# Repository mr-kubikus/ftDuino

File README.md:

# ftDuino
ftDuino controller board

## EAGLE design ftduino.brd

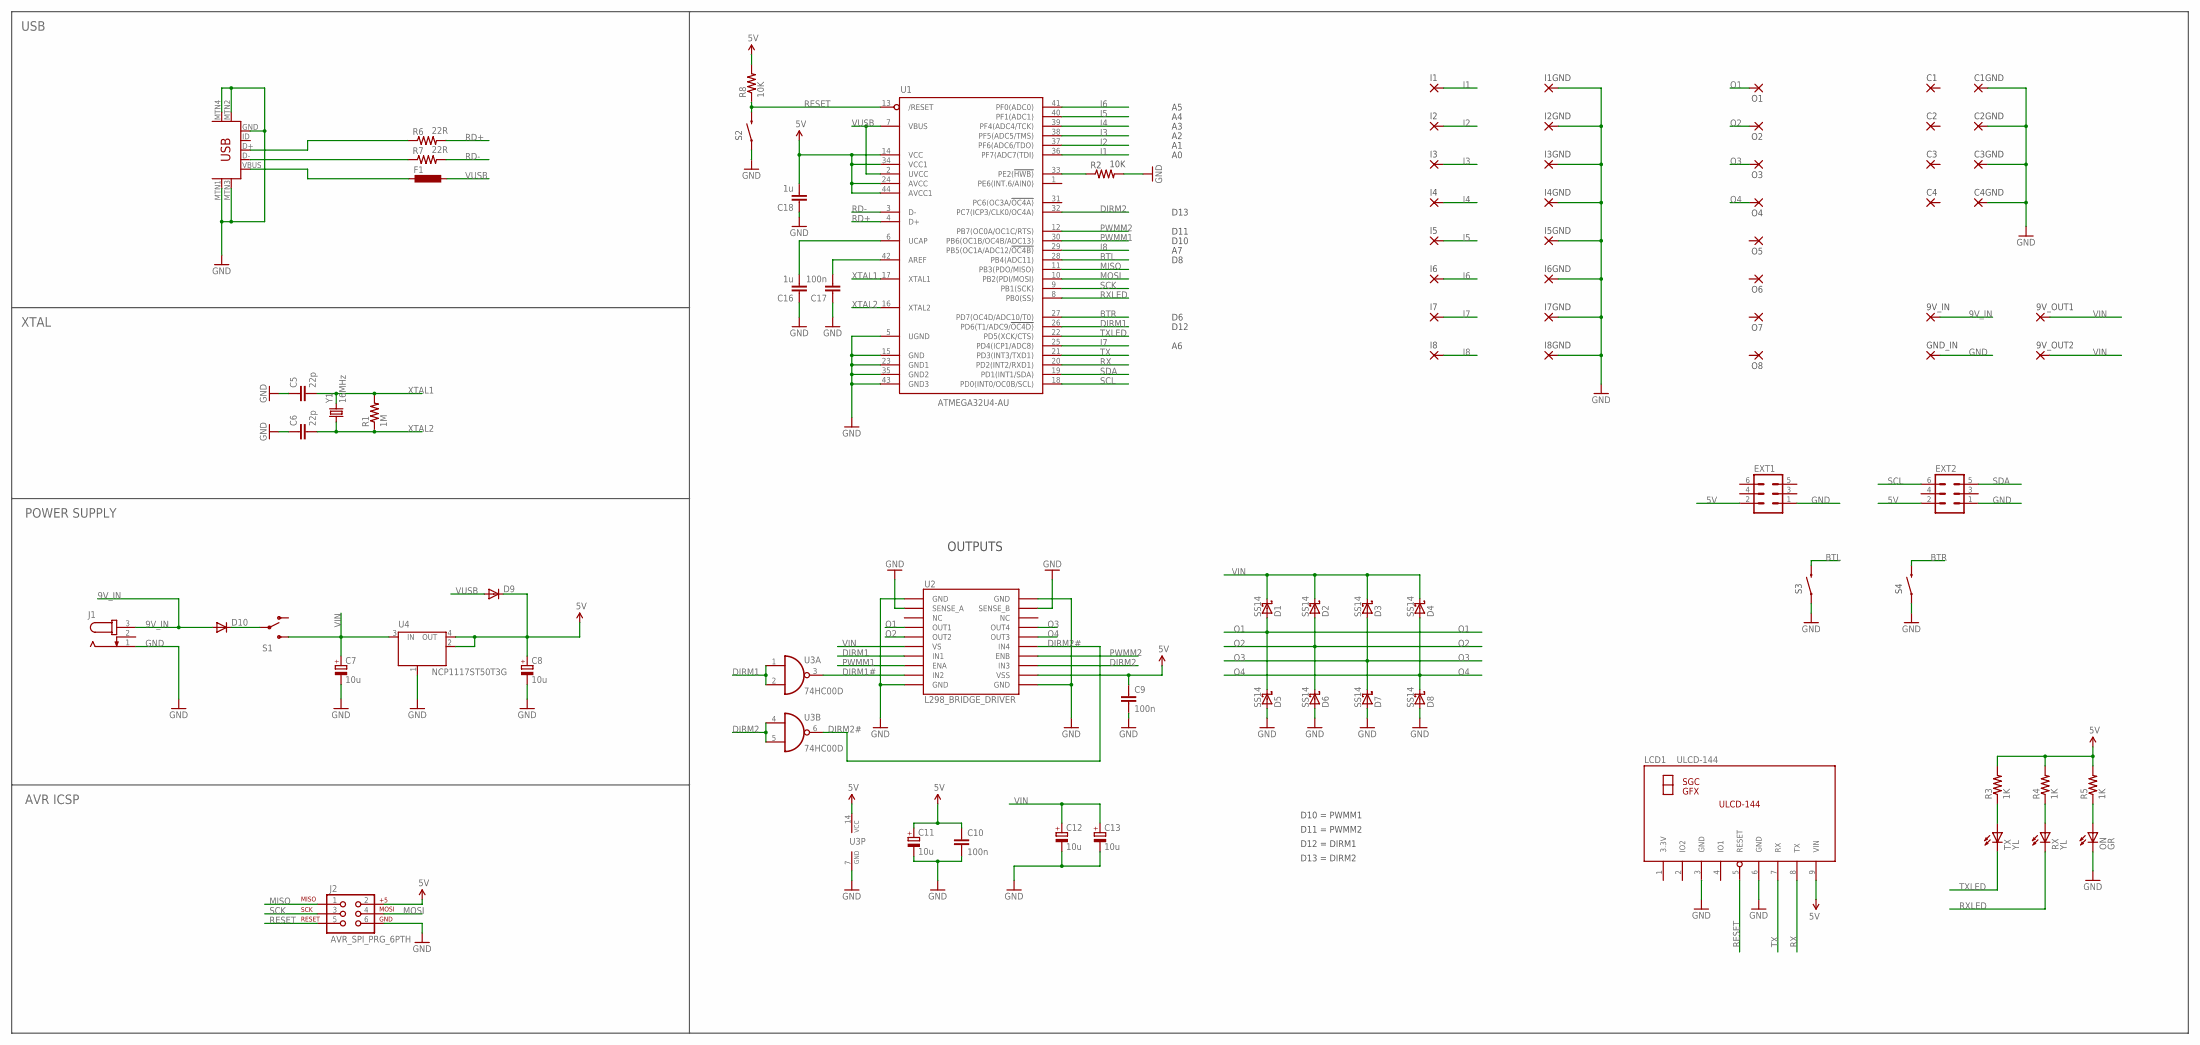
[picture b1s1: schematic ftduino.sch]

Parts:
9V_IN, 9V_OUT1, 9V_OUT2: 5,0/3,2
C1, C1GND, C2, C2GND, C3, C3GND, C4, C4GND: 5,0/3,2
C5, C6: 22p; 0603-CAP
C7, C8, C11, C12, C13: 10u; SMC_B
C9, C10, C17: 100n; 0603-CAP
C16, C18: 1u; 0603-CAP
D1, D2, D3, D4, D5, D6, D7, D8: SS14; SMA
D9, D10: DIODE-SMB; SMB
EXT1, EXT2: MA03-2
F1: L-EUL1812; L1812
GND_IN: 5,0/3,2
I1, I1GND, I2, I2GND, I3, I3GND, I4, I4GND, I5, I5GND, I6, I6GND, I7, I7GND, I8, I8GND: 5,0/3,2
J1: JACK-PLUG1; JK3.5/1.8
J2: AVR_SPI_PRG_6PTH; 2X3
LCD1: ULCD-144
O1, O2, O3, O4, O5, O6, O7, O8: 5,0/3,2
ON: GR; CHIPLED_0805
R1: 1M; 0603-RES
R2, R8: 10K; 0603-RES
R3, R4, R5: 1K; 0603-RES
R6, R7: 22R; 0603-RES
RX: YL; CHIPLED_0805
S1: SWITCH-SPSTPTH; SWITCH-SPDT
S2, S3, S4: SWITCH-MOMENTARY-2PTH; TACTILE-PTH
TX: YL; CHIPLED_0805
U1: ATMEGA32U4-AU; TQFP44
U2: L298_BRIDGE_DRIVER; POWERSO20
U3: 74HC00D; SO14
U4: NCP1117ST50T3G; SOT223
X1: USB-MINIB-5PIN; USB-MINIB
Y1: 16MHz; CTS406

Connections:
3.3V: LCD1.1 (3.3V)
5V: C8.+, C9.1, C10.1, C11.+, C18.2, D9.C, EXT1.2, EXT2.2, J2.2, LCD1.9 (VIN), R3.2, R4.2, R5.2, R8.2, U1.14 (VCC), U1.24 (AVCC), U1.34 (VCC1), U1.44 (AVCC1), U2.12 (VSS), U3.14 (VCC), U4.2 (OUT), U4.4 (OUT)
9V_IN: 9V_IN.1, D10.A, J1.3
BTL: S3.3 (2), U1.28 (PB4(ADC11))
BTR: S4.3 (2), U1.27 (PD7(OC4D/ADC10/T0))
DIRM1: U1.26 (PD6(T1/ADC9/!OC4D)), U2.7 (IN1), U3.1 (I0), U3.2 (I1)
DIRM1#: U2.9 (IN2), U3.3 (O)
DIRM2: U1.32 (PC7(ICP3/CLK0/OC4A)), U2.13 (IN3), U3.4 (I0), U3.5 (I1)
DIRM2#: U2.15 (IN4), U3.6 (O)
GND: C1GND.1, C2GND.1, C3GND.1, C4GND.1, C5.1, C6.1, C7.-, C8.-, C9.2, C10.2, C11.-, C12.-, C13.-, C16.1, C17.1, C18.1, D5.A, D6.A, D7.A, D8.A, EXT1.1, EXT2.1, GND_IN.1, I1GND.1, I2GND.1, I3GND.1, I4GND.1, I5GND.1, I6GND.1, I7GND.1, I8GND.1, J1.1, J2.6, LCD1.3 (GND), LCD1.6 (GND), ON.C, R2.2, S2.1, S3.1, S4.1, U1.5 (UGND), U1.15 (GND), U1.23 (GND1), U1.35 (GND2), U1.43 (GND3), U2.1 (GND), U2.2 (SENSE_A), U2.10 (GND), U2.11 (GND), U2.19 (SENSE_B), U2.20 (GND), U3.7 (GND), U4.1 (GND/ADJ), X1.GND, X1.MTN1 (MTN2), X1.MTN2 (MTN3), X1.MTN3 (MTN1), X1.MTN4
I1: I1.1, U1.36 (PF7(ADC7(TDI))
I2: I2.1, U1.37 (PF6(ADC6/TDO))
I3: I3.1, U1.38 (PF5(ADC5/TMS))
I4: I4.1, U1.39 (PF4(ADC4/TCK))
I5: I5.1, U1.40 (PF1(ADC1))
I6: I6.1, U1.41 (PF0(ADC0))
I7: I7.1, U1.25 (PD4(ICP1/ADC8))
I8: I8.1, U1.29 (PB5(OC1A/ADC12/!OC4B))
MISO: J2.1, U1.11 (PB3(PDO/MISO))
MOSI: J2.4, U1.10 (PB2(PDI/MOSI))
unnamed: C17.2, U1.42 (AREF)
unnamed: C16.2, U1.6 (UCAP)
unnamed: R3.1, TX.A
unnamed: R4.1, RX.A
unnamed: ON.A, R5.1
unnamed: R6.1, X1.D+
unnamed: R7.1, X1.D-
unnamed: R2.1, U1.33 (PE2(!HWB))
unnamed: F1.2, X1.VBUS
unnamed: D10.C, S1.2
O1: D1.A, D5.C, O1.1, U2.4 (OUT1)
O2: D2.A, D6.C, O2.1, U2.5 (OUT2)
O3: D3.A, D7.C, O3.1, U2.17 (OUT4)
O4: D4.A, D8.C, O4.1, U2.16 (OUT3)
PWMM1: U1.30 (PB6(OC1B/OC4B/ADC13)), U2.8 (ENA)
PWMM2: U1.12 (PB7(OC0A/OC1C/RTS)), U2.14 (ENB)
RD+: R6.2, U1.4 (D+)
RD-: R7.2, U1.3 (D-)
RESET: J2.5, LCD1.5 (RESET), R8.1, S2.3 (2), U1.13 (/RESET)
RX: LCD1.8 (TX), U1.20 (PD2(INT2/RXD1))
RXLED: RX.C, U1.8 (PB0(SS))
SCK: J2.3, U1.9 (PB1(SCK))
SCL: EXT2.6, U1.18 (PD0(INT0/OC0B/SCL))
SDA: EXT2.5, U1.19 (PD1(INT1/SDA))
TX: LCD1.7 (RX), U1.21 (PD3(INT3/TXD1))
TXLED: TX.C, U1.22 (PD5(XCK/CTS))
VIN: 9V_OUT1.1, 9V_OUT2.1, C7.+, C12.+, C13.+, D1.C, D2.C, D3.C, D4.C, S1.3 (S), U2.6 (VS), U4.3 (IN)
VUSB: D9.A, F1.1, U1.2 (UVCC), U1.7 (VBUS)
XTAL1: C5.2, R1.2, U1.17 (XTAL1), Y1.3 (2)
XTAL2: C6.2, R1.1, U1.16 (XTAL2), Y1.1

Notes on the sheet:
POWER SUPPLY
OUTPUTS
USB
D10 = PWMM1
D11 = PWMM2
D12 = DIRM1
D13 = DIRM2
XTAL
D10
D11
D12
D13
AVR ICSP

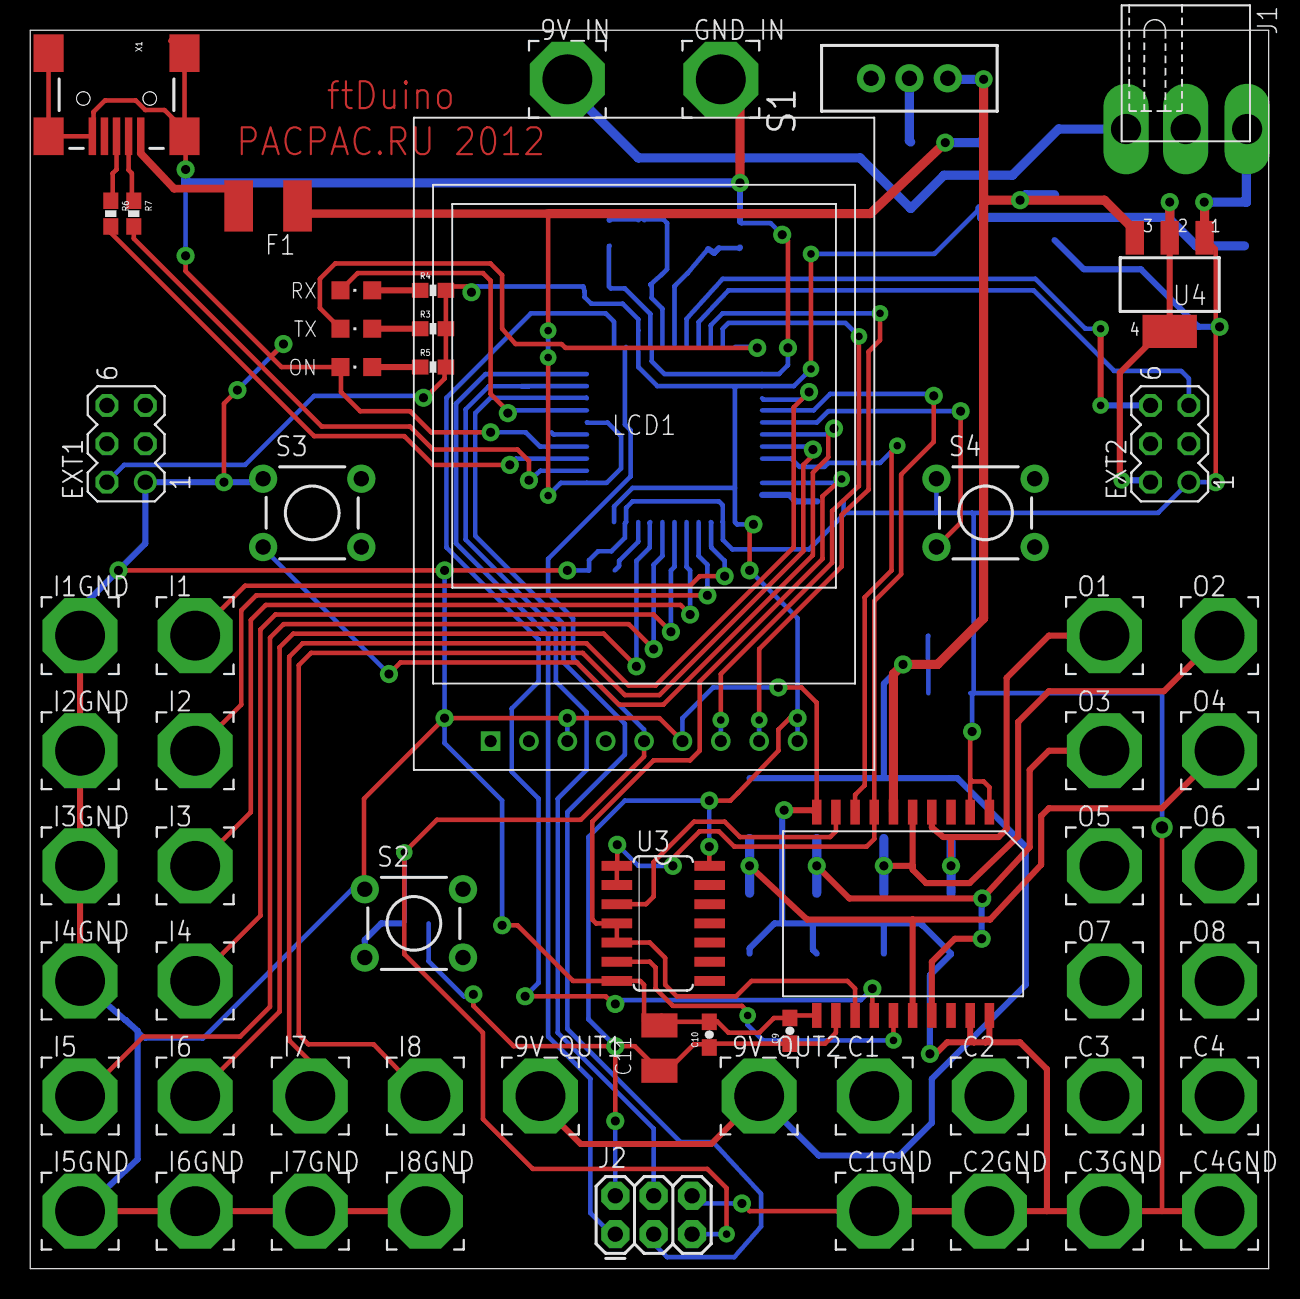
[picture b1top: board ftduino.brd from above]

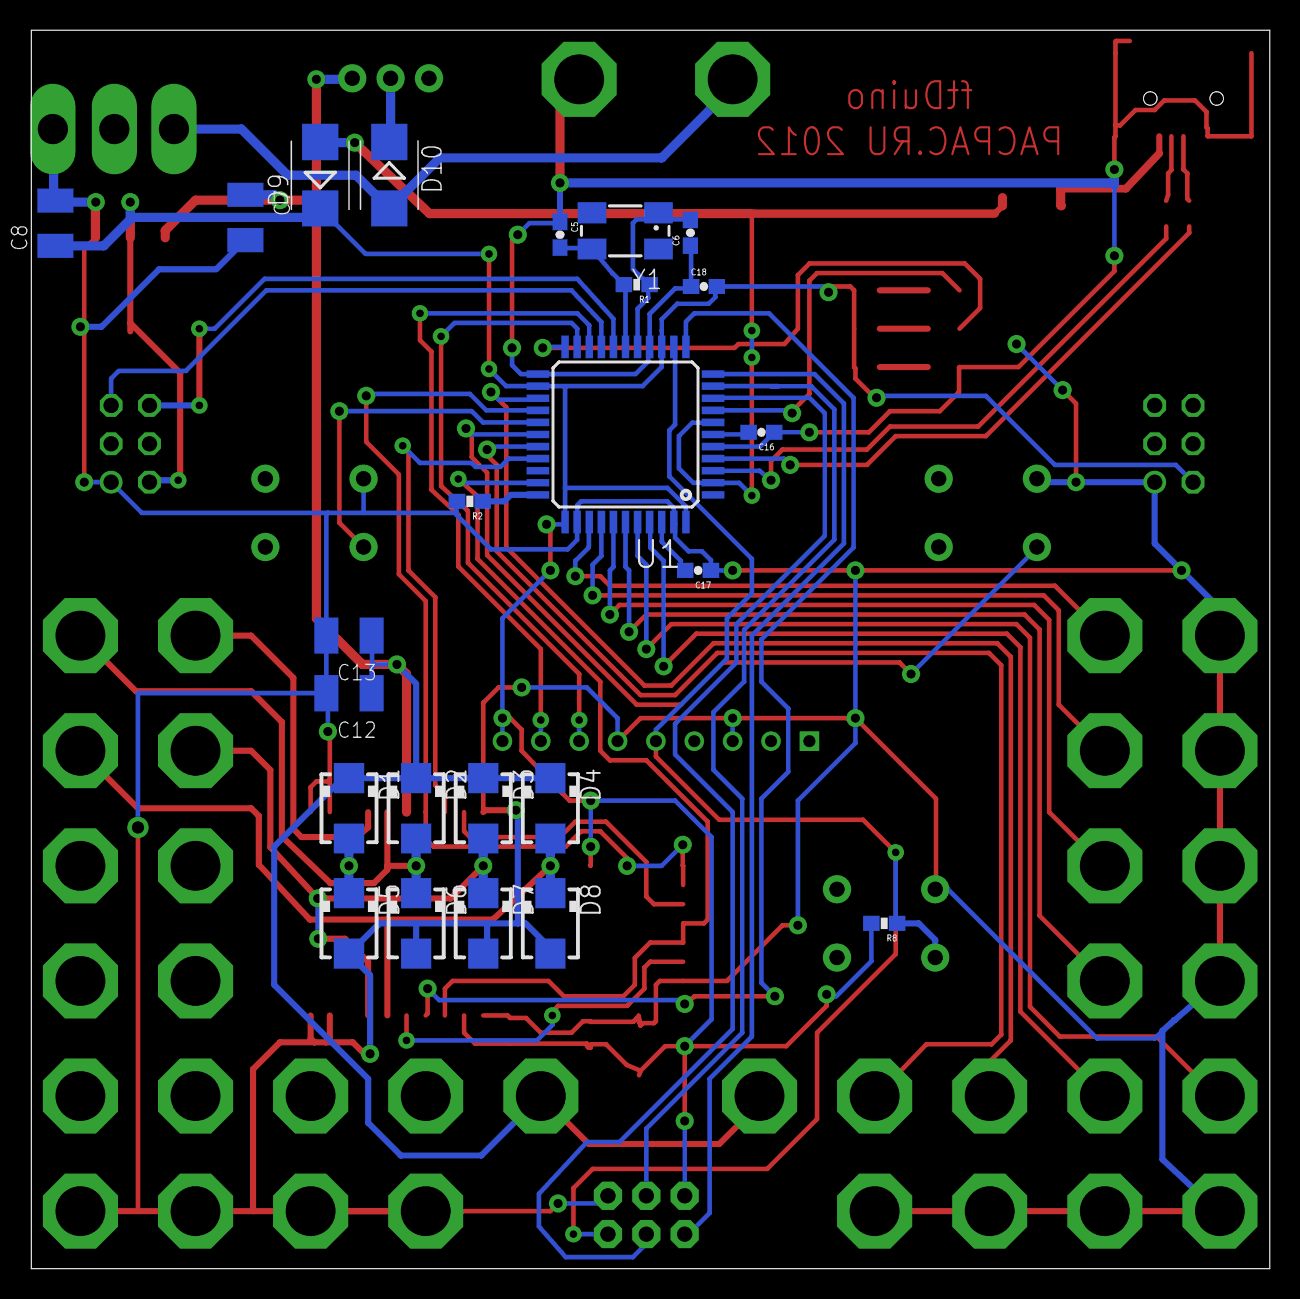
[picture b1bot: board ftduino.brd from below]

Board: 2 copper layers, 82.0 x 82.0 mm, 85 parts (24 on the bottom side), 49 nets.

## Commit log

2017-11-02 Add files via upload
    Initial commit

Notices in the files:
parts and their libraries:
SparkFun: Licensing: CC v3.0 Share-Alike You are welcome to use this library for commercial purposes.
